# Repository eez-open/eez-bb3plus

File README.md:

### This is a WORK IN PROGRESS!

---

### Ownership and License
The contributors are listed in CONTRIB.TXT. 

Licenses | OSHWA UID
--|--
 | 

### Introduction

EEZ BB3+ was conceived as a successor to the BB3 project, which would bring a number of modifications and improvements. 
The following modifications are planned:

* [x] Combining 3 existing core modules ([power supply](https://github.com/eez-open/modular-psu/tree/master/aux-ps), [MCU](https://github.com/eez-open/modular-psu/tree/master/mcu) and [backplane](https://github.com/eez-open/modular-psu/tree/master/bp3c)) into a single mainboard
* [x] Enlarge TFT touchscreen from 4.3" (480x272) resistive to 5" (800x480) capacitive
* [x] Increase fan size from Ø80 to 92 mm
* [x] Single main power rail +12V (45/60 W)
* [x] Introducing half width modules and increasing the total number of modules from 3 full-width to 5 half-width (or two 1½-width)
* [x] TFT Display PCB with 4 user switch/hot keys

Planned new features of BB3+:

* [x] Max. 5 peripheral modules
* [x] Soft-power switch with standby indication
* [x] Isolated UART and RS485 port (with Modbus support) on the rear panel
* [x] Power/Sense terminals for the first two modules on the rear panel
* [x] MCU/CPU module slot [Raspberry Pi CM5](https://www.raspberrypi.com/products/compute-module-5/) compatible
* [x] M.2 slot, Key M (for NVMe SSD)
* [x] External display output (e.g. HDMI® or DisplayPort™ compatible): GUI and data could be displayed simultaneously on TFT and external display
* [x] 2.0/3.0 USB Hub with _FlexConnect_
* [x] 10/100/1000 Mbps Ethernet port
* [x] USB-C on the front panel, 2x USB 3 on the rear panel
* [x] Low-jitter 10 MHz reference clock
* [x] Trigger switch matrix (8 sources, 6 destinations)
* [x] New DIB specification for peripheral modules communication introducing USB HS/SS and PCIe
* **CE certified design**

### Modules

* [5" DVID TFT display](https://github.com/eez-open/eez-bb3plus/tree/main/KiCad/TFT%20module) module (HDMI® compatible input, optional EDID EEPROM, capacitive or optional resistive touchscreen)
* [BIO2210](https://github.com/eez-open/eez-bb3plus/tree/main/KiCad/BIO2210) Basic **non-isolated** I/O module: protected 8 analog inputs, 2 analog outputs, 8 multi-level (1.8 / 3.3 / 5 V) digital inputs, I2C/SMBus, 7 multi-level (1.8 / 3.3 V) digital outputs, 7 low-side switches, programmable clock, 3.3, 5 and 12V power outputs with reverse current blocking
* [DIB2 Adapter](https://github.com/eez-open/eez-bb3plus/tree/main/KiCad/DIB2%20adapter) module (USB3 Type A, DIB2 I/O, Reference clock)

### Experimental designs

During development, several prototypes will be used for features planned for BB3+. Information about them can be found in the [Experimental](https://github.com/eez-open/eez-bb3plus/tree/main/Experimental)  subfolder.

### Related topics and links

* [EEZ BB3+ MCU](https://github.com/eez-open/eez-bb3plus-cm5-mcu) module
* [DIB DCP405+](https://github.com/eez-open/dib-dcp405plus) power module
* [DIB MIO168+](https://github.com/eez-open/dib-mio168plus) mixed I/O module
* [EEZ BB3](https://github.com/eez-open/modular-psu)
* [EEZ Studio](https://www.envox.eu/studio/studio-introduction)
* [Discord](https://discord.com/invite/q5KAeeenNG) server
* [X](https://x.com/envox) (ex Twitter)
* [YouTube](https://www.youtube.com/c/eezopen) channel
* [EEVblog forum](https://www.eevblog.com/forum/projects/eez-h25005-a-possible-successor-of-eez-h24005-programmable-power-supply/) discussion

---

This work is financed by [NLnet](https://nlnet.nl/project/BB3-CM5/) foundation

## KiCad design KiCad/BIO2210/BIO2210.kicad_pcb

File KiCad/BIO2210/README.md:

Licenses | OSHWA UID
--|--
 | 

### BB3+ BIO2210 module

**Non-isolated**  Basic I/O module

* 32-bit MCU, 250 MHz
* 8-ch protected analog inputs (multiplexed): 2 x 0-100 V, 6 x 0-10 V
* 2-ch protected analog outputs near zero to 10 V
* 1.8 / 3.3 / 5 V logic level protected 8 digital input (alternative function: SPI and UART)
* 1.8 / 3.3 V logic level protected 7 digital outputs (alternative function: SPI, PWM, programmable clock output) + AC Freq output
* 7 low-side switches
* Protected 1.8 / 3.3 V I2C/SMBus interface
* 3.3V, 5V and 12V fused power outputs with reverse current blocking
* SPI and USB communication with BB3+ main processor
* Over-voltage fault indication for digital I/O

### Resources

* [Theory of operation](../../docs/BIO2210)
* [PDF Schematics](../../schematic-diagram/BIO2210.pdf)
* [Interactive BOM](../../fabrication/bom/BIO2210/ibom.html)

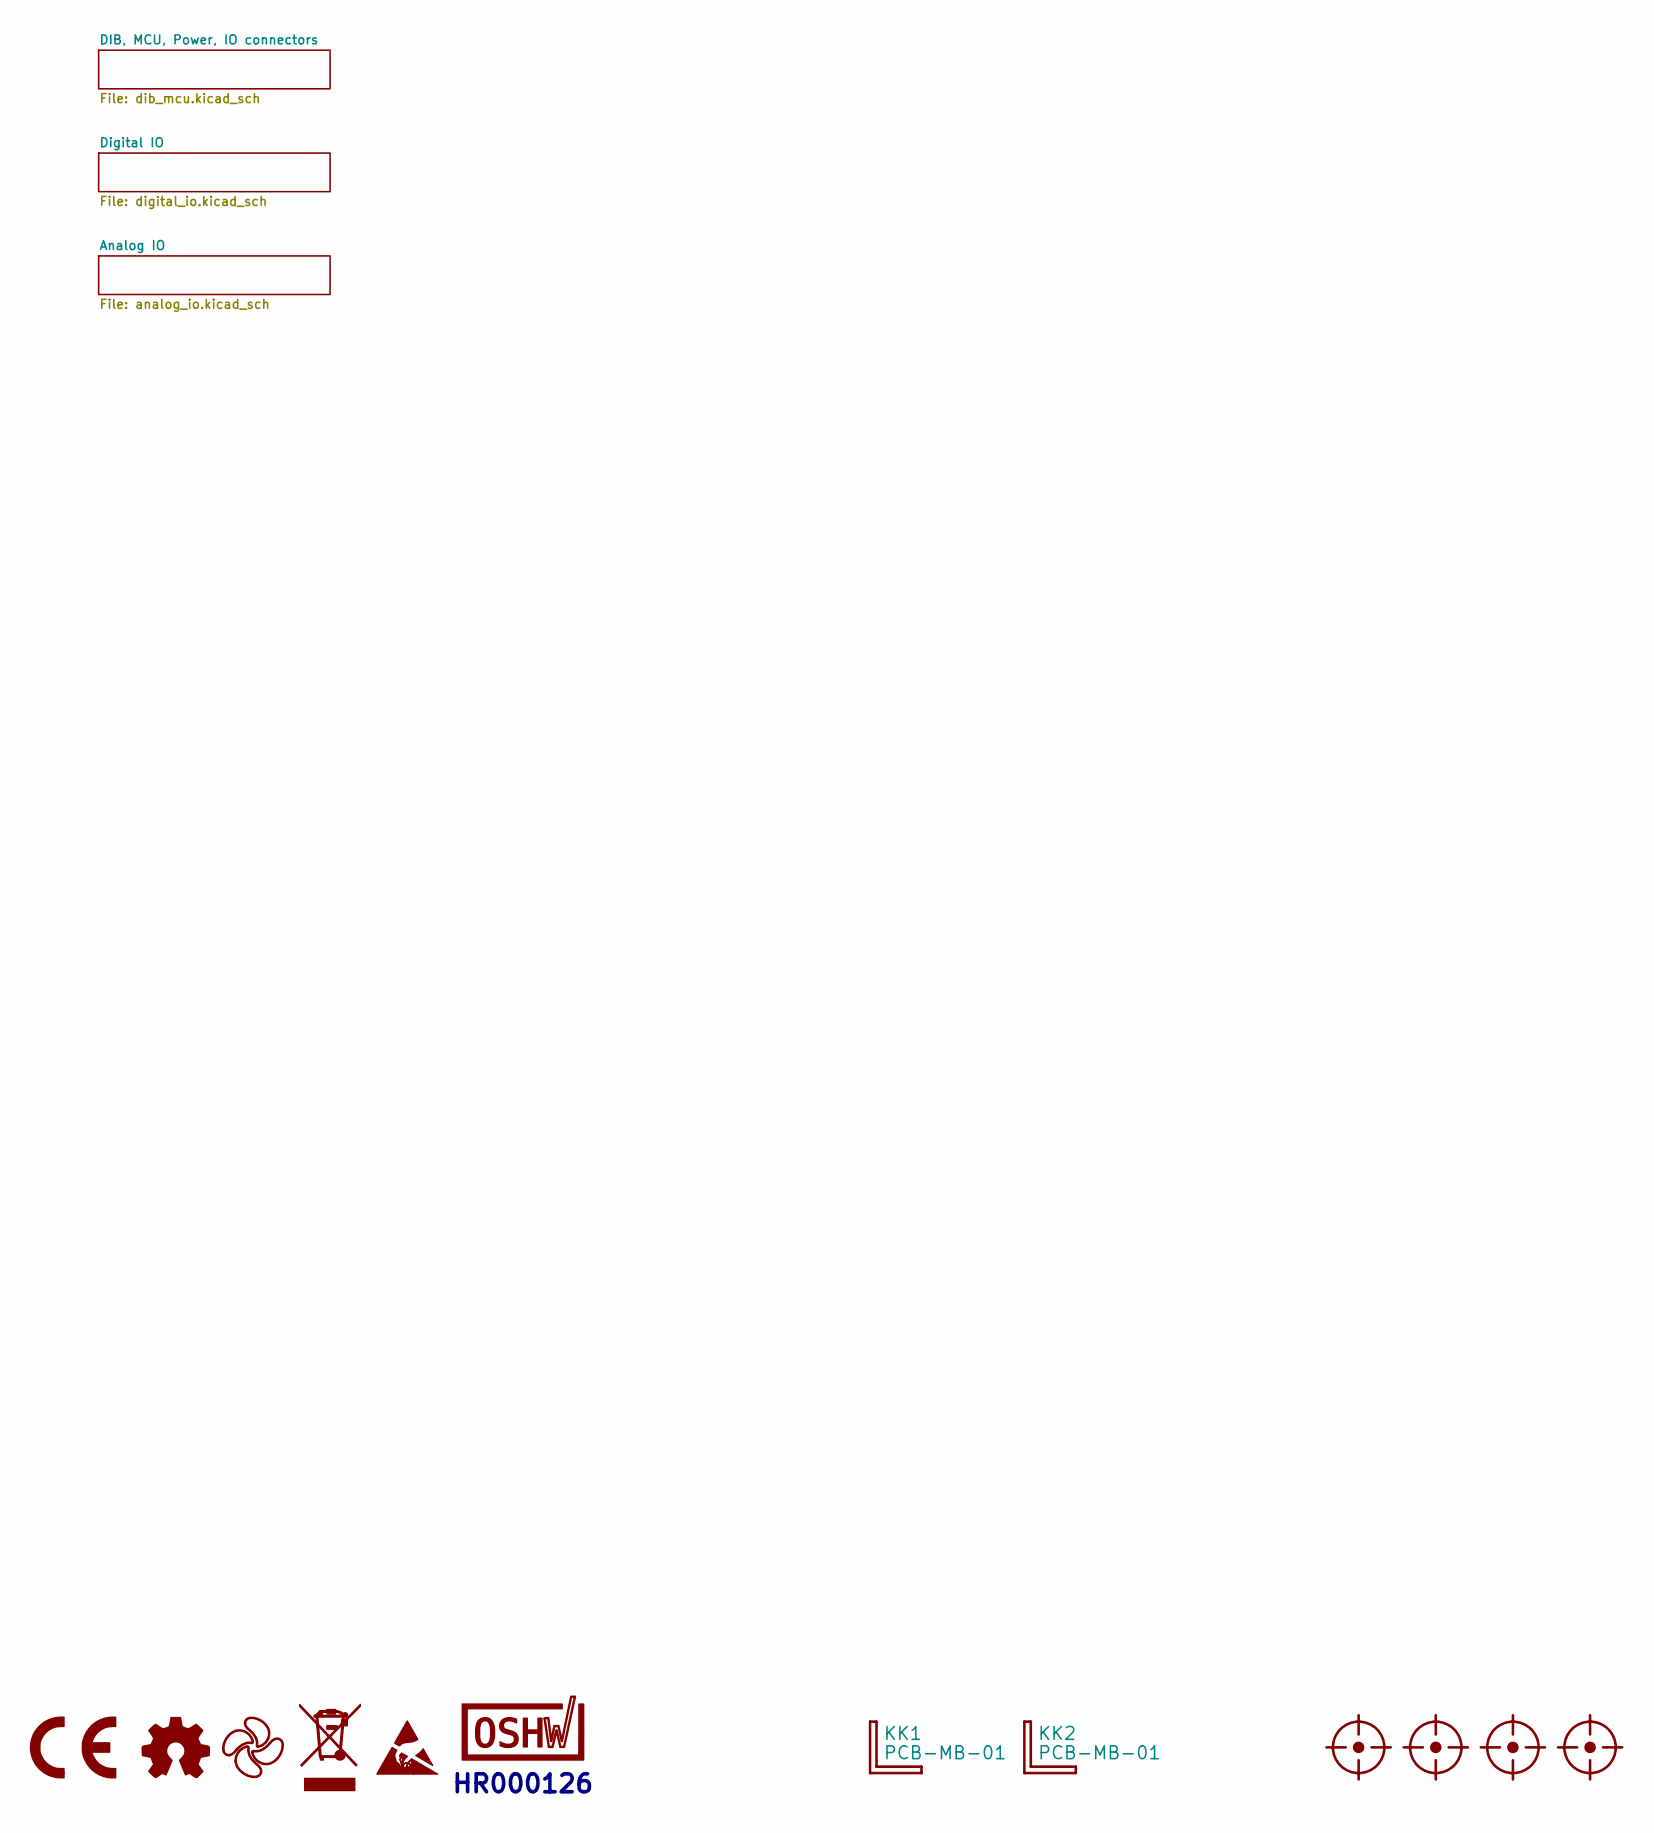
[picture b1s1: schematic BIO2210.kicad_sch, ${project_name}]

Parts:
FM1, FM2, FM3, FM4: FIDUCIAL; Fiducial_0.75mm_Mask1.5mm
KK1, KK2: PCB-MB-01; DigiKey RPC1760-ND
LOGO1: CR logo; CE logo
LOGO2: Open HW logo
LOGO3: EEZ logo; EEZ logo (outline 6mm)
LOGO4: WEEE logo
LOGO5: ESD logo
LOGO6: OSHWA logo; OSHWA logo 6.6mm

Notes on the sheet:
HR000126

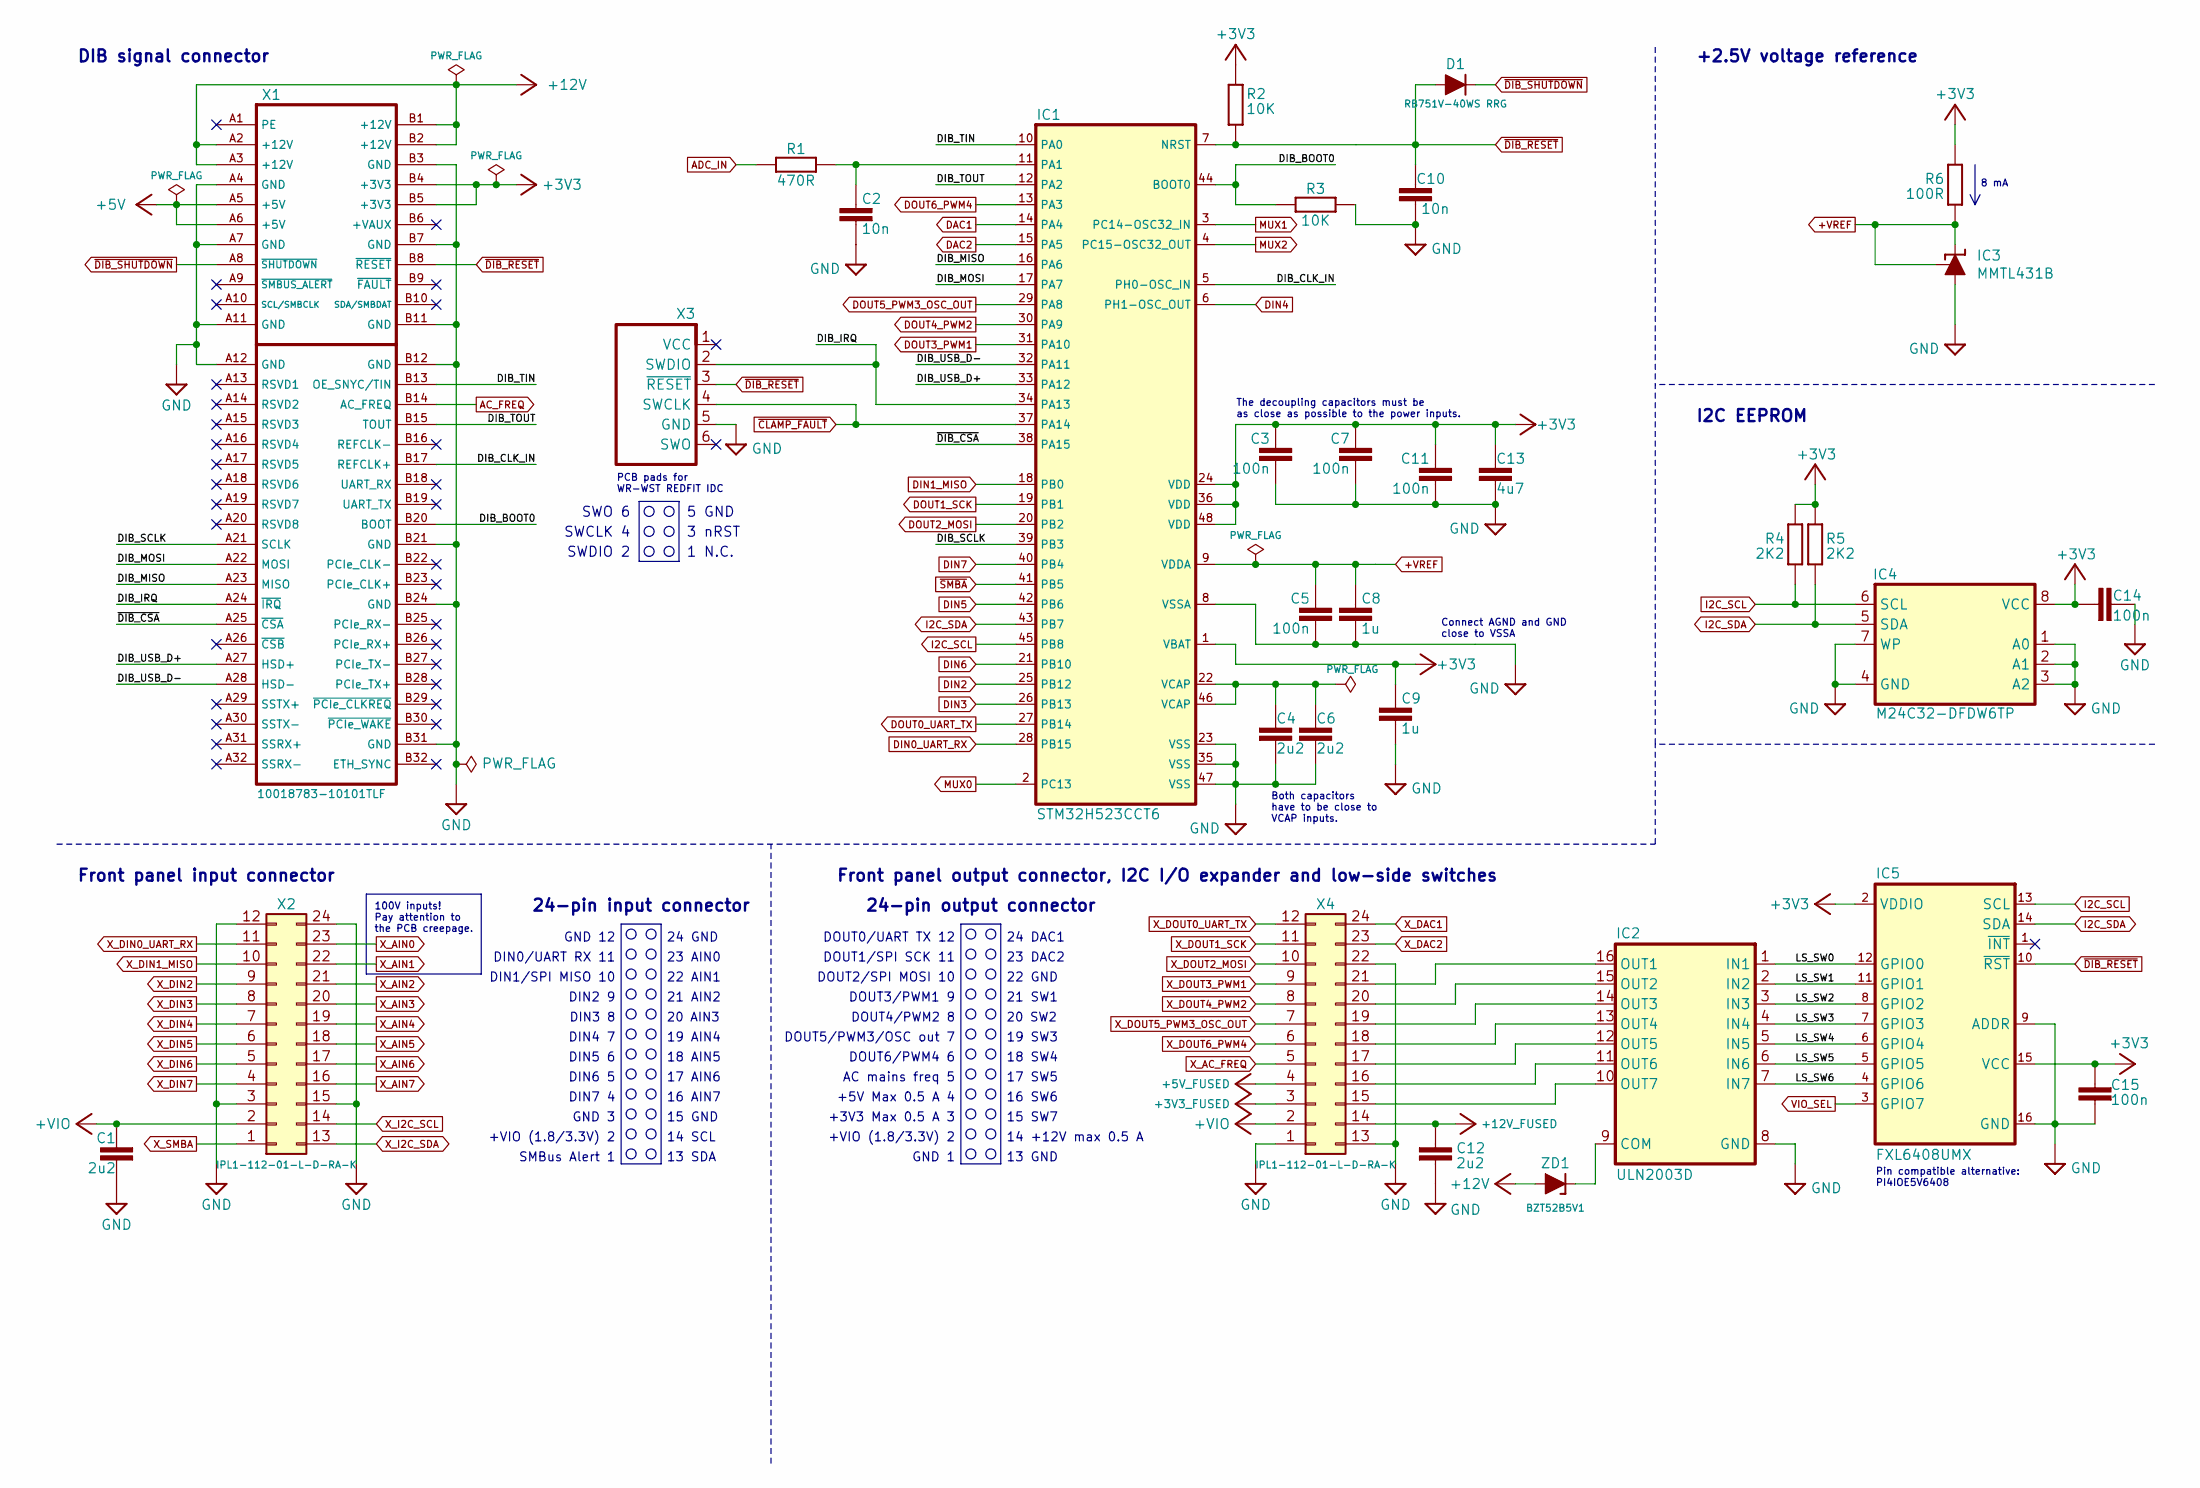
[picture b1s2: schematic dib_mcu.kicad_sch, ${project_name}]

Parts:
C1, C4, C6, C12: 2u2; C_0603_1608Metric; DigiKey 490-12332-1-ND
C2, C10: 10n; C_0603_1608Metric; DigiKey 1276-1009-1-ND
C3, C5, C7, C11, C14, C15: 100n; C_0603_1608Metric; DigiKey 1276-6717-1-ND
C8, C9: 1u; C_0603_1608Metric; DigiKey 1276-CL10A105KA8NFNCCT-ND
C13: 4u7; C_0805_2012Metric; DigiKey 1276-CL21A475KACLRNCCT-ND
D1: RB751V-40WS RRG; SOD-323_1P8X1P35_ONS-M; DigiKey RB751V-40WSRRGCT-ND
IC1: STM32H523CCT6; LQFP-48_7X7MM; DigiKey 497-STM32H523CCT6-ND
IC2: ULN2003D; SO16; DigiKey 497-2345-1-ND
IC3: MMTL431B; SOT103P240X110-3N; DigiKey 4878-MMTL431BCT-ND
IC4: M24C32-DFDW6TP; TSSOP-8; DigiKey 497-16067-1-ND
IC5: FXL6408UMX; UMLP16_1P8X2P6_ONS; DigiKey FXL6408UMXCT-ND
R1: 470R; R_1206_3216Metric; DigiKey RMCF1206FT470RCT-ND
R2, R3: 10K; R_0603_1608Metric; DigiKey 13-RC0603FR-1310KLCT-ND
R4, R5: 2K2; R_0603_1608Metric; DigiKey YAG1296CT-ND
R6: 100R; R_0603_1608Metric; DigiKey 13-RC0603FR-10100RLCT-ND
X1: 10018783-10101TLF; DIB 2.0 edge card connector
X2, X4: IPL1-112-01-L-D-RA-K; SAMTEC_IPL1-112-01-X-D-RA-K; DigiKey SAM9610-ND
X3: N.C.; WR-WST_490107670612_DEBUG
ZD1: BZT52B5V1; SOD123; DigiKey 5399-BZT52B5V1CT-ND

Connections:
+3V3: C3.1, C7.1, C9.2, C11.1, C13.1, C14.1, C15.2, IC1.1 (VBAT), IC1.24 (VDD), IC1.36 (VDD), IC1.48 (VDD), IC4.8 (VCC), IC5.2 (VDDIO), IC5.15 (VCC), R2.2, R4.1, R5.1, R6.2, X1.B4 (+3V3), X1.B5 (+3V3); also elsewhere on the board
+3V3_FUSED: X4.3; also elsewhere on the board
+5V: X1.A5 (+5V), X1.A6 (+5V); also elsewhere on the board
+5V_FUSED: X4.4; also elsewhere on the board
+12V: X1.A2 (+12V), X1.A3 (+12V), X1.B1 (+12V), X1.B2 (+12V), ZD1.A; also elsewhere on the board
+12V_FUSED: C12.2, X4.14; also elsewhere on the board
+VIO: C1.2, X2.2, X4.2; also elsewhere on the board
+VREF: C5.1, C8.2, IC1.9 (VDDA), IC3.1 (C), IC3.2 (R), R6.1; also elsewhere on the board
/DIB, MCU, Power, IO connectors/DIB_BOOT0: IC1.44 (BOOT0), R3.2, X1.B20 (BOOT)
/DIB, MCU, Power, IO connectors/DIB_CLK_IN: IC1.5 (PH0-OSC_IN), X1.B17 (REFCLK+)
/DIB, MCU, Power, IO connectors/DIB_IRQ: IC1.34 (PA13), X1.A24 (~IRQ), X3.2 (SWDIO)
/DIB, MCU, Power, IO connectors/DIB_MISO: IC1.16 (PA6), X1.A23 (MISO)
/DIB, MCU, Power, IO connectors/DIB_MOSI: IC1.17 (PA7), X1.A22 (MOSI)
/DIB, MCU, Power, IO connectors/DIB_SCLK: IC1.39 (PB3), X1.A21 (SCLK)
/DIB, MCU, Power, IO connectors/DIB_TIN: IC1.10 (PA0), X1.B13 (OE_SNYC/TIN)
/DIB, MCU, Power, IO connectors/DIB_TOUT: IC1.12 (PA2), X1.B15 (TOUT)
/DIB, MCU, Power, IO connectors/DIB_USB_D+: IC1.33 (PA12), X1.A27 (HSD+)
/DIB, MCU, Power, IO connectors/DIB_USB_D-: IC1.32 (PA11), X1.A28 (HSD-)
/DIB, MCU, Power, IO connectors/LS_SW0: IC2.1 (IN1), IC5.12 (GPIO0)
/DIB, MCU, Power, IO connectors/LS_SW1: IC2.2 (IN2), IC5.11 (GPIO1)
/DIB, MCU, Power, IO connectors/LS_SW2: IC2.3 (IN3), IC5.8 (GPIO2)
/DIB, MCU, Power, IO connectors/LS_SW3: IC2.4 (IN4), IC5.7 (GPIO3)
/DIB, MCU, Power, IO connectors/LS_SW4: IC2.5 (IN5), IC5.6 (GPIO4)
/DIB, MCU, Power, IO connectors/LS_SW5: IC2.6 (IN6), IC5.5 (GPIO5)
/DIB, MCU, Power, IO connectors/LS_SW6: IC2.7 (IN7), IC5.4 (GPIO6)
/DIB, MCU, Power, IO connectors/~DIB_CSA: IC1.38 (PA15), X1.A25 (~CSA)
AC_FREQ: X1.B14 (AC_FREQ); also elsewhere on the board
ADC_IN: R1.2; also elsewhere on the board
DAC1: IC1.14 (PA4); also elsewhere on the board
DAC2: IC1.15 (PA5); also elsewhere on the board
DIN0_UART_RX: IC1.28 (PB15); also elsewhere on the board
DIN1_MISO: IC1.18 (PB0); also elsewhere on the board
DIN2: IC1.25 (PB12); also elsewhere on the board
DIN3: IC1.26 (PB13); also elsewhere on the board
DIN4: IC1.6 (PH1-OSC_OUT); also elsewhere on the board
DIN5: IC1.42 (PB6); also elsewhere on the board
DIN6: IC1.21 (PB10); also elsewhere on the board
DIN7: IC1.40 (PB4); also elsewhere on the board
DOUT0_UART_TX: IC1.27 (PB14); also elsewhere on the board
DOUT1_SCK: IC1.19 (PB1); also elsewhere on the board
DOUT2_MOSI: IC1.20 (PB2); also elsewhere on the board
DOUT3_PWM1: IC1.31 (PA10); also elsewhere on the board
DOUT4_PWM2: IC1.30 (PA9); also elsewhere on the board
DOUT5_PWM3_OSC_OUT: IC1.29 (PA8); also elsewhere on the board
DOUT6_PWM4: IC1.13 (PA3); also elsewhere on the board
GND: C1.1, C2.2, C3.2, C4.1, C5.2, C6.1, C7.2, C8.1, C9.1, C10.1, C11.2, C12.1, C13.2, C14.2, C15.1, IC1.8 (VSSA), IC1.23 (VSS), IC1.35 (VSS), IC1.47 (VSS), IC2.8 (GND), IC3.3 (A), IC4.1 (A0), IC4.2 (A1), IC4.3 (A2), IC4.4 (GND), IC4.7 (WP), IC5.9 (ADDR), IC5.16 (GND), R3.1, X1.A4 (GND), X1.A7 (GND), X1.A11 (GND), X1.A12 (GND), X1.B3 (GND), X1.B7 (GND), X1.B11 (GND), X1.B12 (GND), X1.B21 (GND), X1.B24 (GND), X1.B31 (GND), X2.3, X2.12, X2.15, X2.24, X3.5 (GND), X4.1, X4.13, X4.22; also elsewhere on the board
I2C_SCL: IC1.45 (PB8), IC4.6 (SCL), IC5.13 (SCL), R4.2; also elsewhere on the board
I2C_SDA: IC1.43 (PB7), IC4.5 (SDA), IC5.14 (SDA), R5.2; also elsewhere on the board
MUX0: IC1.2 (PC13); also elsewhere on the board
MUX1: IC1.3 (PC14-OSC32_IN); also elsewhere on the board
MUX2: IC1.4 (PC15-OSC32_OUT); also elsewhere on the board
unnamed: C4.2, C6.2, IC1.22 (VCAP), IC1.46 (VCAP)
unnamed: C2.1, IC1.11 (PA1), R1.1
unnamed: IC2.9 (COM), ZD1.C
unnamed: IC2.16 (OUT1), X4.21
unnamed: IC2.15 (OUT2), X4.20
unnamed: IC2.14 (OUT3), X4.19
unnamed: IC2.13 (OUT4), X4.18
unnamed: IC2.12 (OUT5), X4.17
unnamed: IC2.11 (OUT6), X4.16
unnamed: IC2.10 (OUT7), X4.15
VIO_SEL: IC5.3 (GPIO7); also elsewhere on the board
X_AC_FREQ: X4.5; also elsewhere on the board
X_AIN0: X2.23; also elsewhere on the board
X_AIN1: X2.22; also elsewhere on the board
X_AIN2: X2.21; also elsewhere on the board
X_AIN3: X2.20; also elsewhere on the board
X_AIN4: X2.19; also elsewhere on the board
X_AIN5: X2.18; also elsewhere on the board
X_AIN6: X2.17; also elsewhere on the board
X_AIN7: X2.16; also elsewhere on the board
X_DAC1: X4.24; also elsewhere on the board
X_DAC2: X4.23; also elsewhere on the board
X_DIN0_UART_RX: X2.11; also elsewhere on the board
X_DIN1_MISO: X2.10; also elsewhere on the board
X_DIN2: X2.9; also elsewhere on the board
X_DIN3: X2.8; also elsewhere on the board
X_DIN4: X2.7; also elsewhere on the board
X_DIN5: X2.6; also elsewhere on the board
X_DIN6: X2.5; also elsewhere on the board
X_DIN7: X2.4; also elsewhere on the board
X_DOUT0_UART_TX: X4.12; also elsewhere on the board
X_DOUT1_SCK: X4.11; also elsewhere on the board
X_DOUT2_MOSI: X4.10; also elsewhere on the board
X_DOUT3_PWM1: X4.9; also elsewhere on the board
X_DOUT4_PWM2: X4.8; also elsewhere on the board
X_DOUT5_PWM3_OSC_OUT: X4.7; also elsewhere on the board
X_DOUT6_PWM4: X4.6; also elsewhere on the board
X_I2C_SCL: X2.14; also elsewhere on the board
X_I2C_SDA: X2.13; also elsewhere on the board
X_SMBA: X2.1; also elsewhere on the board
~CLAMP_FAULT: IC1.37 (PA14), X3.4 (SWCLK); also elsewhere on the board
~DIB_RESET: C10.2, D1.A, IC1.7 (NRST), IC5.10 (~RST), R2.1, X1.B8 (~RESET), X3.3 (~RESET)
~DIB_SHUTDOWN: D1.C, X1.A8 (~SHUTDOWN); also elsewhere on the board
~SMBA: IC1.41 (PB5); also elsewhere on the board

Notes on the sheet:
19 SW3
24 DAC1
SWCLK 4
GND 1
Both capacitors have to be close to VCAP inputs.
SWDIO 2
14 +12V max 0.5 A
DOUT3/PWM1 9
+2.5V voltage reference
14 SCL
Front panel input connector
8 mA
DIN1/SPI MISO 10
DIN3 8
16 SW6
I2C EEPROM
22 GND
DOUT1/SPI SCK 11
DOUT2/SPI MOSI 10
PCB pads for WR-WST REDFIT IDC
DIN7 4
SMBus Alert 1
3 nRST
SWO 6
Front panel output connector, I2C I/O expander and low-side switches
5 GND
23 DAC2
DIN2 9
19 AIN4
DIN6 5
18 SW4
17 SW5
20 SW2
17 AIN6
+VIO (1.8/3.3V) 2
24-pin output connector
DOUT4/PWM2 8
DIN0/UART RX 11
DOUT0/UART TX 12
24-pin input connector

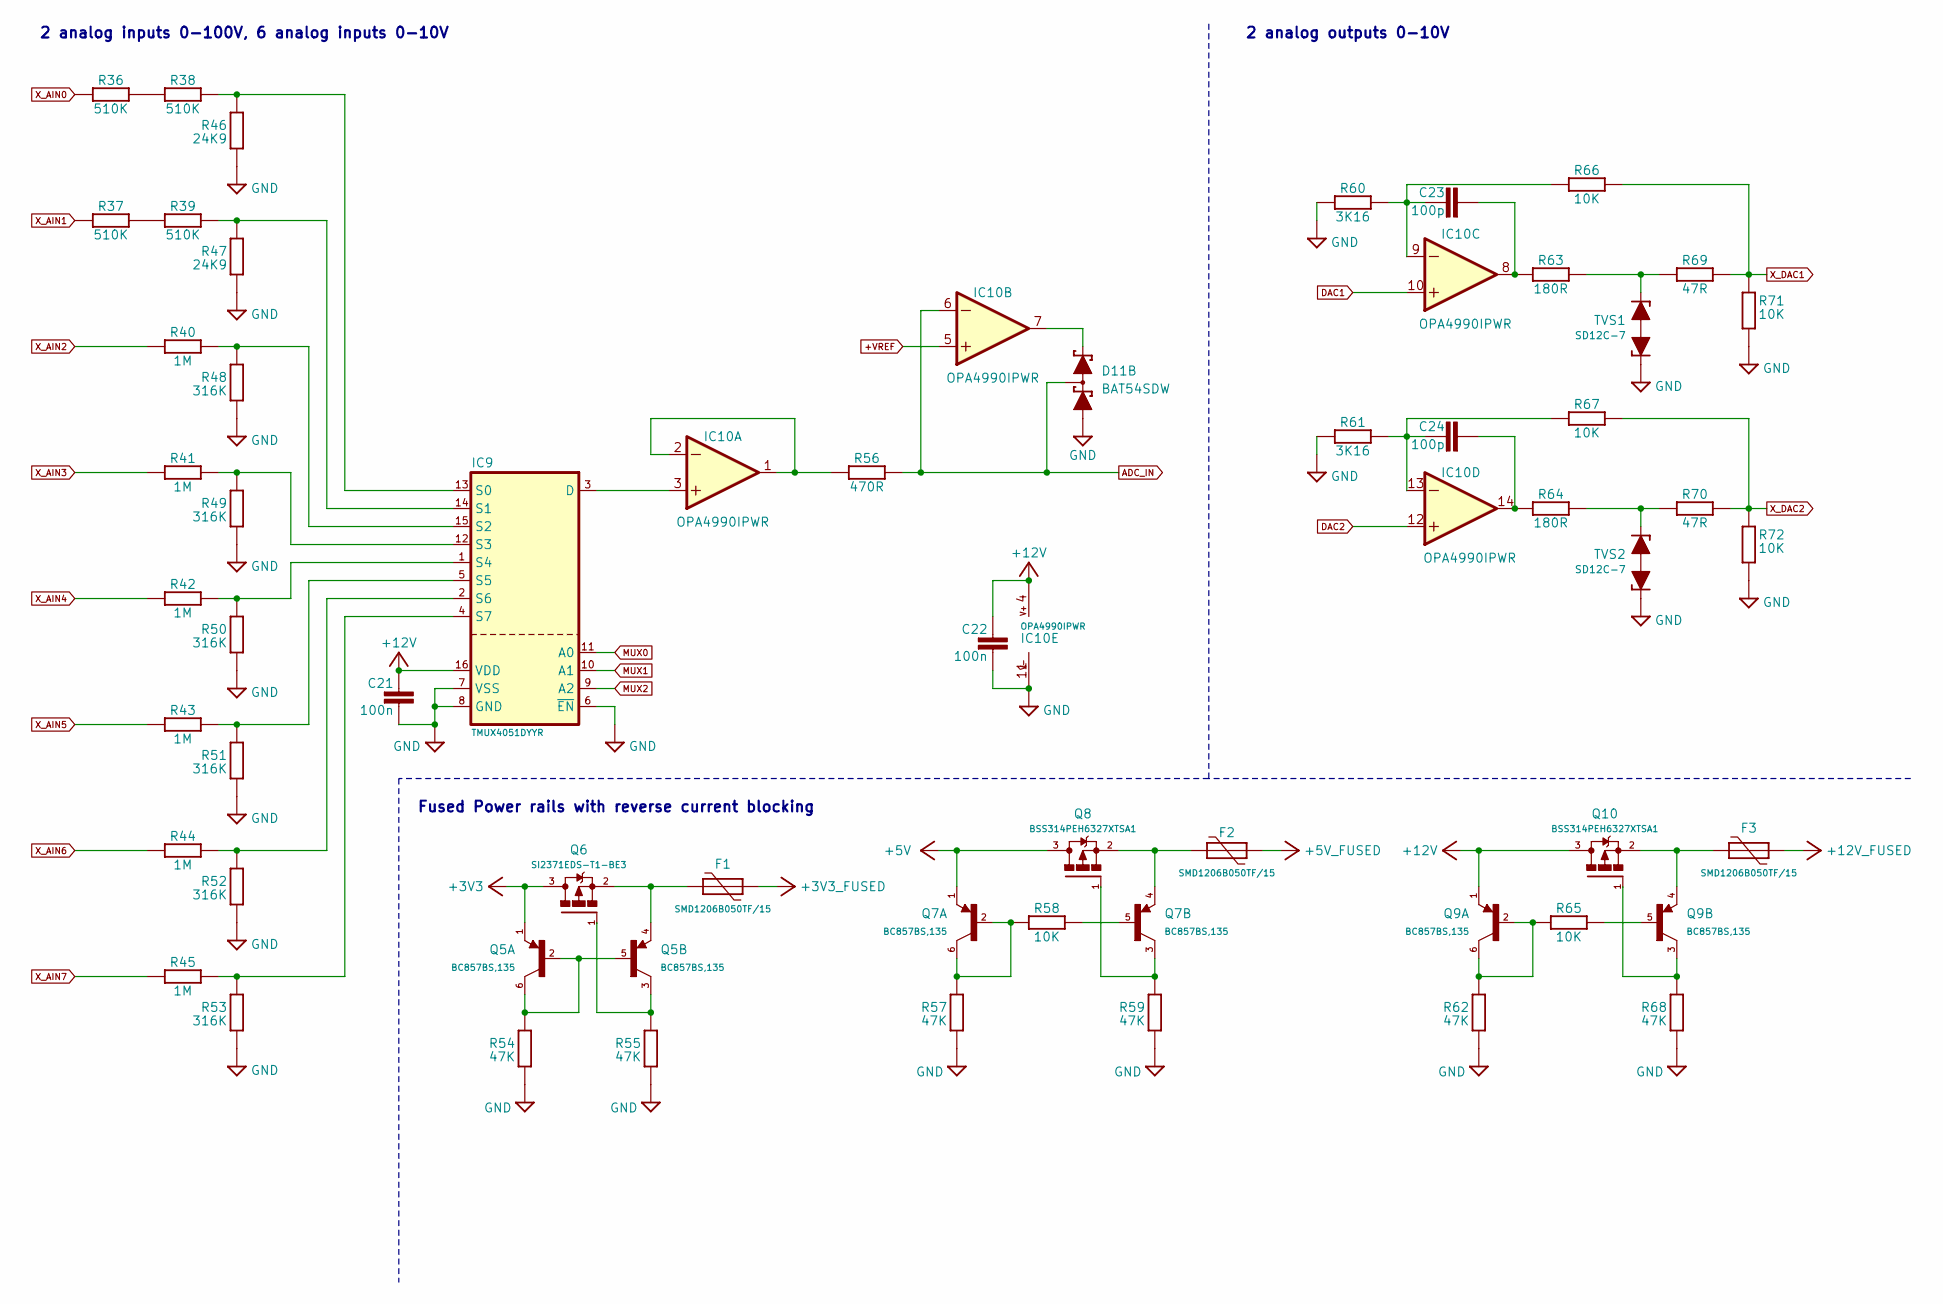
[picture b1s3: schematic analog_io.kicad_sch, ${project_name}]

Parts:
C21, C22: 100n; C_0603_1608Metric; DigiKey 1276-6717-1-ND
C23, C24: 100p; C_0603_1608Metric; DigiKey 1276-1295-1-ND
D11: BAT54SDW; SOP65P210X110-6N; DigiKey 3757-BAT54SDW_R1_00001CT-ND
F1, F2, F3: SMD1206B050TF/15; Fuse_1206; DigiKey 13-SMD1206B050TF/15CT-ND
IC9: TMUX4051DYYR; SOT-23-THIN16_DYY_TEX; DigiKey 296-TMUX4051DYYRCT-ND
IC10: OPA4990IPWR; PW14; DigiKey 296-OPA4990IPWRCT-ND
Q5, Q7, Q9: BC857BS,135; SOT65P210X110-6N; DigiKey 1727-1881-1-ND
Q6: SI2371EDS-T1-BE3; SOT23-3; DigiKey 742-SI2371EDS-T1-BE3CT-ND
Q8, Q10: BSS314PEH6327XTSA1; SOT23-3; DigiKey BSS314PEH6327XTSA1CT-ND
R36, R37, R38, R39: 510K; R_1206_3216Metric; DigiKey RMCF1206FT510KCT-ND
R40, R41, R42, R43, R44, R45: 1M; R_1206_3216Metric; DigiKey RMCF1206FT1M00CT-ND
R46, R47: 24K9; R_1206_3216Metric; DigiKey RMCF1206FT24K9CT-ND
R48, R49, R50, R51, R52, R53: 316K; R_1206_3216Metric; DigiKey 738-RMCF1206FT316KCT-ND
R54, R55, R57, R59, R62, R68: 47K; R_0603_1608Metric; DigiKey 13-RC0603FR-1347KLCT-ND
R56: 470R; R_1206_3216Metric; DigiKey RMCF1206FT470RCT-ND
R58, R65, R66, R67, R71, R72: 10K; R_0603_1608Metric; DigiKey 13-RC0603FR-1310KLCT-ND
R60, R61: 3K16; R_0603_1608Metric; DigiKey 311-3.16KHRCT-ND
R63, R64: 180R; R_1206_3216Metric; DigiKey 13-RC1206FR-13180RLCT-ND
R69, R70: 47R; R_0805_2012Metric; DigiKey 311-47.0CRCT-ND
TVS1, TVS2: SD12C-7; SOD-323_PESD; DigiKey 31-SD12C-7CT-ND

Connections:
+3V3: Q5.1 (E1), Q6.3 (D); also elsewhere on the board
+3V3_FUSED: F1.1; also elsewhere on the board
+5V: Q7.1 (E1), Q8.3 (D); also elsewhere on the board
+5V_FUSED: F2.1; also elsewhere on the board
+12V: C21.1, C22.1, IC9.16 (VDD), IC10.4 (V+), Q9.1 (E1), Q10.3 (D); also elsewhere on the board
+12V_FUSED: F3.1; also elsewhere on the board
+VREF: IC10.5 (+IN); also elsewhere on the board
ADC_IN: D11.3 (A3K4), IC10.6 (-IN), R56.1; also elsewhere on the board
DAC1: IC10.10 (+IN); also elsewhere on the board
DAC2: IC10.12 (+IN); also elsewhere on the board
GND: C21.2, C22.2, D11.4 (A4), IC9.6 (~EN), IC9.7 (VSS), IC9.8 (GND), IC10.11 (V-), R46.1, R47.1, R48.1, R49.1, R50.1, R51.1, R52.1, R53.1, R54.2, R55.2, R57.2, R59.2, R60.2, R61.2, R62.2, R68.2, R71.1, R72.1, TVS1.C1 (1), TVS2.C1 (1); also elsewhere on the board
MUX0: IC9.11 (A0); also elsewhere on the board
MUX1: IC9.10 (A1); also elsewhere on the board
MUX2: IC9.9 (A2); also elsewhere on the board
unnamed: D11.5 (K3), IC10.7 (OUT)
unnamed: IC9.13 (S0), R38.1, R46.2
unnamed: IC9.14 (S1), R39.1, R47.2
unnamed: IC9.15 (S2), R40.1, R48.2
unnamed: IC9.12 (S3), R41.1, R49.2
unnamed: IC9.1 (S4), R42.1, R50.2
unnamed: IC9.5 (S5), R43.1, R51.2
unnamed: IC9.2 (S6), R44.1, R52.2
unnamed: IC9.4 (S7), R45.1, R53.2
unnamed: IC9.3 (D), IC10.3 (+IN)
unnamed: IC10.1 (OUT), IC10.2 (-IN), R56.2
unnamed: C23.2, IC10.9 (-IN), R60.1, R66.2
unnamed: C23.1, IC10.8 (OUT), R63.2
unnamed: C24.2, IC10.13 (-IN), R61.1, R67.2
unnamed: C24.1, IC10.14 (OUT), R64.2
unnamed: Q5.2 (B1), Q5.5 (B2), Q5.6 (C1), R54.1
unnamed: Q5.3 (C2), Q6.1 (G), R55.1
unnamed: F1.2, Q5.4 (E2), Q6.2 (S)
unnamed: Q7.2 (B1), Q7.6 (C1), R57.1, R58.2
unnamed: Q7.5 (B2), R58.1
unnamed: Q7.3 (C2), Q8.1 (G), R59.1
unnamed: F2.2, Q7.4 (E2), Q8.2 (S)
unnamed: Q9.2 (B1), Q9.6 (C1), R62.1, R65.2
unnamed: Q9.5 (B2), R65.1
unnamed: Q9.3 (C2), Q10.1 (G), R68.1
unnamed: F3.2, Q9.4 (E2), Q10.2 (S)
unnamed: R36.1, R38.2
unnamed: R37.1, R39.2
unnamed: R63.1, R69.2, TVS1.C2 (2)
unnamed: R64.1, R70.2, TVS2.C2 (2)
X_AIN0: R36.2; also elsewhere on the board
X_AIN1: R37.2; also elsewhere on the board
X_AIN2: R40.2; also elsewhere on the board
X_AIN3: R41.2; also elsewhere on the board
X_AIN4: R42.2; also elsewhere on the board
X_AIN5: R43.2; also elsewhere on the board
X_AIN6: R44.2; also elsewhere on the board
X_AIN7: R45.2; also elsewhere on the board
X_DAC1: R66.1, R69.1, R71.2; also elsewhere on the board
X_DAC2: R67.1, R70.1, R72.2; also elsewhere on the board

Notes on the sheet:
2 analog inputs 0-100V, 6 analog inputs 0-10V
2 analog outputs 0-10V
Fused Power rails with reverse current blocking

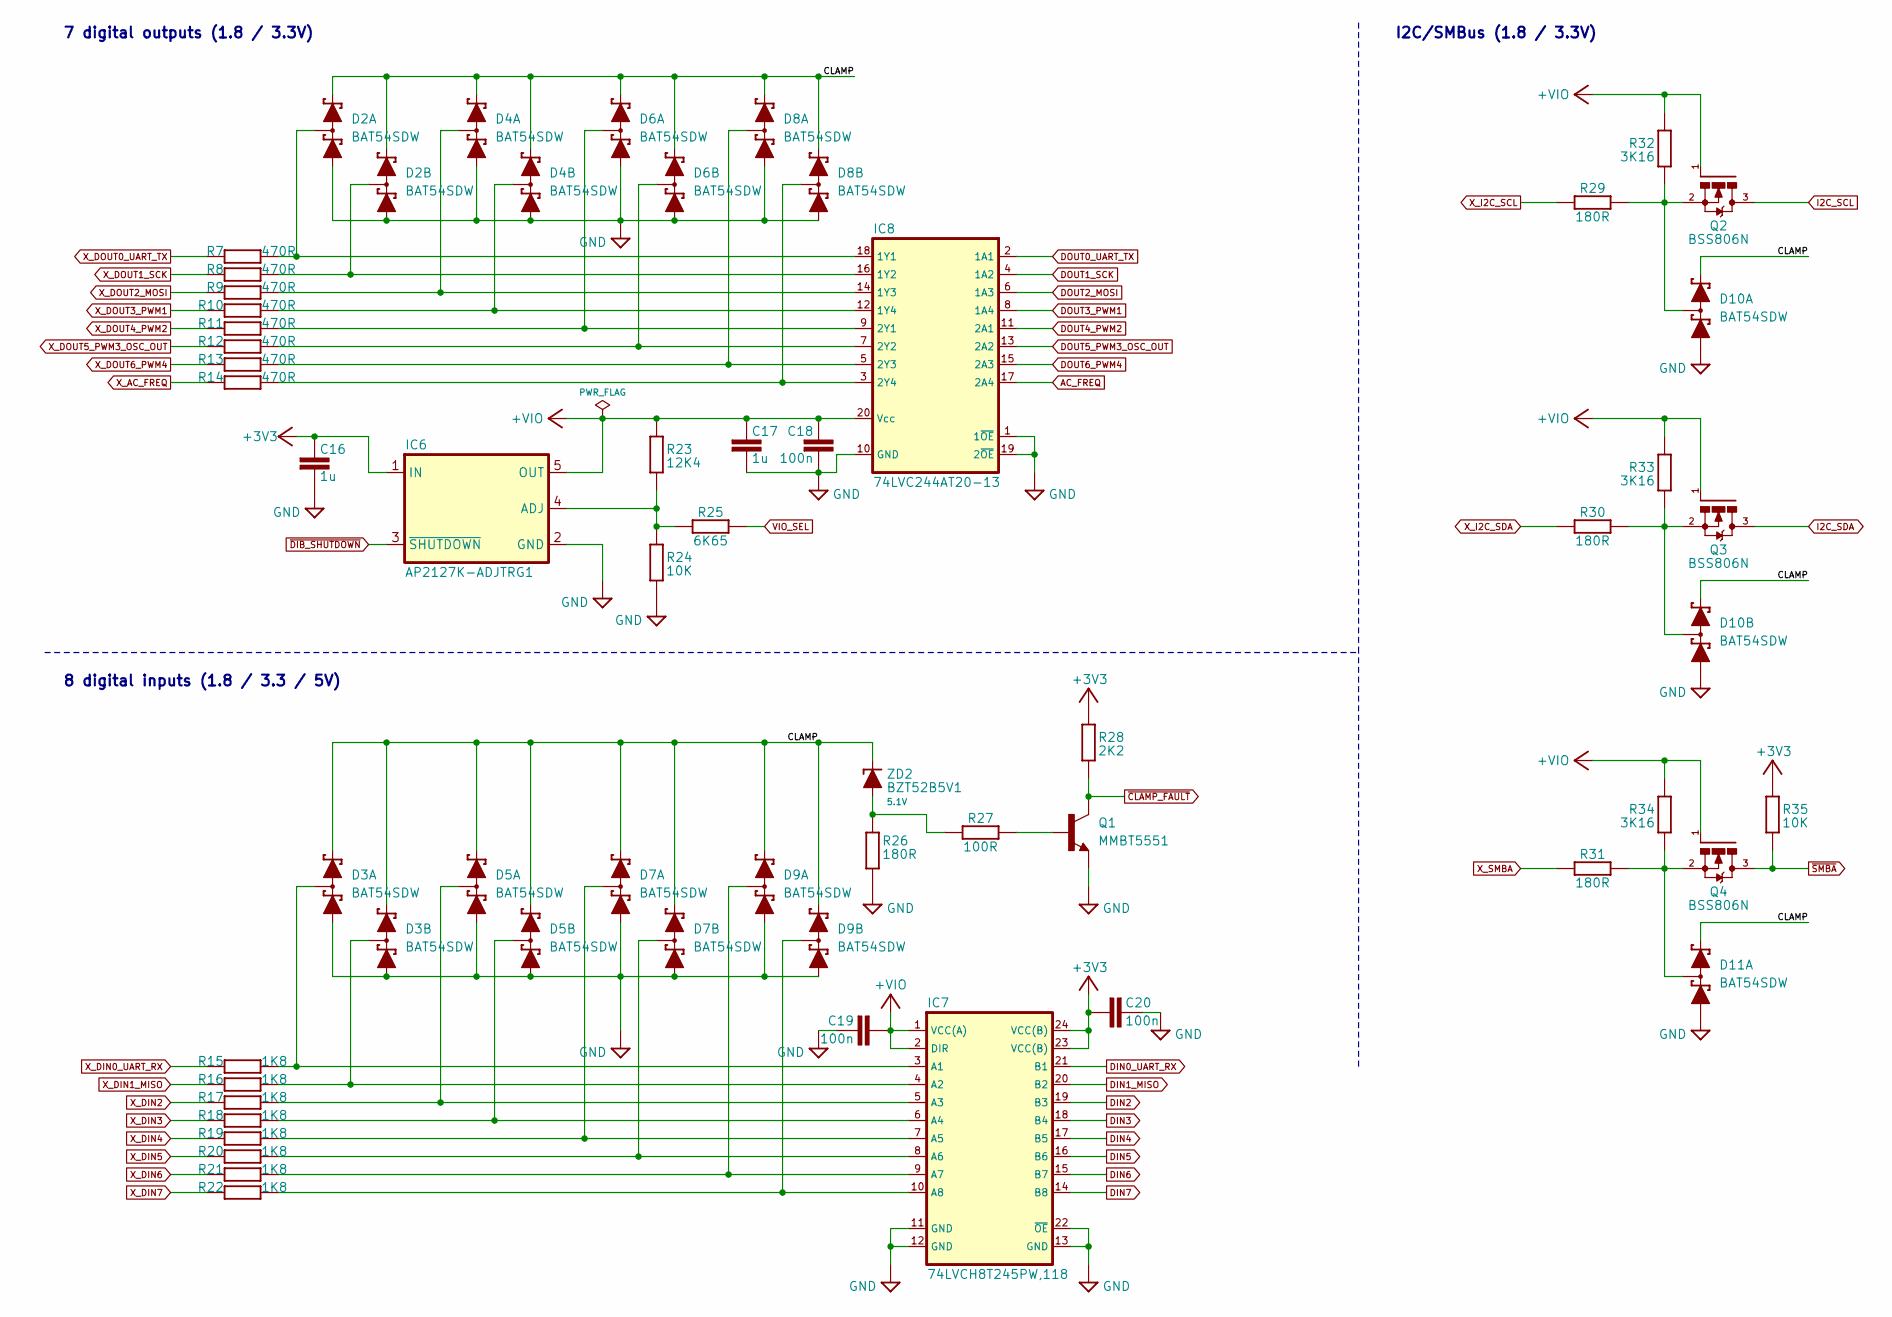
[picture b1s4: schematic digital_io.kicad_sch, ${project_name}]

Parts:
C16, C17: 1u; C_0603_1608Metric; DigiKey 1276-CL10A105KA8NFNCCT-ND
C18, C19, C20: 100n; C_0603_1608Metric; DigiKey 1276-6717-1-ND
D2, D3, D4, D5, D6, D7, D8, D9, D10, D11: BAT54SDW; SOP65P210X110-6N; DigiKey 3757-BAT54SDW_R1_00001CT-ND
IC6: AP2127K-ADJTRG1; DBV5; DigiKey AP2127K-ADJTRG1DICT-ND
IC7: 74LVCH8T245PW,118; TSSOP-24; DigiKey 1727-4419-1-ND
IC8: 74LVC244AT20-13; TSSOP-20; DigiKey 31-74LVC244AT20-13CT-ND
Q1: MMBT5551; SOT23-BEC; DigiKey MMBT5551LT1GOSCT-ND
Q2, Q3, Q4: BSS806N; SOT103P240X110-3N; DigiKey BSS806NEH6327XTSA1CT-ND
R7, R8, R9, R10, R11, R12, R13, R14: 470R; R_1206_3216Metric; DigiKey RMCF1206FT470RCT-ND
R15, R16, R17, R18, R19, R20, R21, R22: 1K8; R_1206_3216Metric; DigiKey RMCF1206FT1K80CT-ND
R23: 12K4; R_0603_1608Metric; DigiKey 311-12.4KMCT-ND
R24, R35: 10K; R_0603_1608Metric; DigiKey 13-RC0603FR-1310KLCT-ND
R25: 6K65; R_0603_1608Metric; DigiKey 311-6.65KHRCT-ND
R26, R29, R30, R31: 180R; R_1206_3216Metric; DigiKey 13-RC1206FR-13180RLCT-ND
R27: 100R; R_0603_1608Metric; DigiKey 13-RC0603FR-10100RLCT-ND
R28: 2K2; R_0603_1608Metric; DigiKey YAG1296CT-ND
R32, R33, R34: 3K16; R_0603_1608Metric; DigiKey 311-3.16KHRCT-ND
ZD2: BZT52B5V1; SOD123; DigiKey 5399-BZT52B5V1CT-ND

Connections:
+3V3: C16.2, C20.1, IC6.1 (IN), IC7.23 (VCC(B)), IC7.24 (VCC(B)), R28.2, R35.2; also elsewhere on the board
+VIO: C17.2, C18.1, C19.1, IC6.5 (OUT), IC7.1 (VCC(A)), IC7.2 (DIR), IC8.20 (Vcc), Q2.1 (G), Q3.1 (G), Q4.1 (G), R23.2, R32.1, R33.1, R34.1; also elsewhere on the board
/Digital IO/CLAMP: D2.2 (K2), D2.5 (K3), D3.2 (K2), D3.5 (K3), D4.2 (K2), D4.5 (K3), D5.2 (K2), D5.5 (K3), D6.2 (K2), D6.5 (K3), D7.2 (K2), D7.5 (K3), D8.2 (K2), D8.5 (K3), D9.2 (K2), D9.5 (K3), D10.2 (K2), D10.5 (K3), D11.2 (K2), ZD2.C
AC_FREQ: IC8.17 (2A4); also elsewhere on the board
DIN0_UART_RX: IC7.21 (B1); also elsewhere on the board
DIN1_MISO: IC7.20 (B2); also elsewhere on the board
DIN2: IC7.19 (B3); also elsewhere on the board
DIN3: IC7.18 (B4); also elsewhere on the board
DIN4: IC7.17 (B5); also elsewhere on the board
DIN5: IC7.16 (B6); also elsewhere on the board
DIN6: IC7.15 (B7); also elsewhere on the board
DIN7: IC7.14 (B8); also elsewhere on the board
DOUT0_UART_TX: IC8.2 (1A1); also elsewhere on the board
DOUT1_SCK: IC8.4 (1A2); also elsewhere on the board
DOUT2_MOSI: IC8.6 (1A3); also elsewhere on the board
DOUT3_PWM1: IC8.8 (1A4); also elsewhere on the board
DOUT4_PWM2: IC8.11 (2A1); also elsewhere on the board
DOUT5_PWM3_OSC_OUT: IC8.13 (2A2); also elsewhere on the board
DOUT6_PWM4: IC8.15 (2A3); also elsewhere on the board
GND: C16.1, C17.1, C18.2, C19.2, C20.2, D2.1 (A1), D2.4 (A4), D3.1 (A1), D3.4 (A4), D4.1 (A1), D4.4 (A4), D5.1 (A1), D5.4 (A4), D6.1 (A1), D6.4 (A4), D7.1 (A1), D7.4 (A4), D8.1 (A1), D8.4 (A4), D9.1 (A1), D9.4 (A4), D10.1 (A1), D10.4 (A4), D11.1 (A1), IC6.2 (GND), IC7.11 (GND), IC7.12 (GND), IC7.13 (GND), IC7.22 (~OE), IC8.1 (1~OE), IC8.10 (GND), IC8.19 (2~OE), Q1.E, R24.1, R26.1; also elsewhere on the board
I2C_SCL: Q2.3 (D); also elsewhere on the board
I2C_SDA: Q3.3 (D); also elsewhere on the board
unnamed: D2.6 (K1A2), IC8.18 (1Y1), R7.2
unnamed: D2.3 (A3K4), IC8.16 (1Y2), R8.2
unnamed: D3.6 (K1A2), IC7.3 (A1), R15.2
unnamed: D3.3 (A3K4), IC7.4 (A2), R16.2
unnamed: D4.6 (K1A2), IC8.14 (1Y3), R9.2
unnamed: D4.3 (A3K4), IC8.12 (1Y4), R10.2
unnamed: D5.6 (K1A2), IC7.5 (A3), R17.2
unnamed: D5.3 (A3K4), IC7.6 (A4), R18.2
unnamed: D6.6 (K1A2), IC8.9 (2Y1), R11.2
unnamed: D6.3 (A3K4), IC8.7 (2Y2), R12.2
unnamed: D7.6 (K1A2), IC7.7 (A5), R19.2
unnamed: D7.3 (A3K4), IC7.8 (A6), R20.2
unnamed: D8.6 (K1A2), IC8.5 (2Y3), R13.2
unnamed: D8.3 (A3K4), IC8.3 (2Y4), R14.2
unnamed: D9.6 (K1A2), IC7.9 (A7), R21.2
unnamed: D9.3 (A3K4), IC7.10 (A8), R22.2
unnamed: D10.6 (K1A2), Q2.2 (S), R29.2, R32.2
unnamed: D10.3 (A3K4), Q3.2 (S), R30.2, R33.2
unnamed: D11.6 (K1A2), Q4.2 (S), R31.2, R34.2
unnamed: IC6.4 (ADJ), R23.1, R24.2, R25.1
unnamed: Q1.B, R27.2
unnamed: R26.2, R27.1, ZD2.A
VIO_SEL: R25.2; also elsewhere on the board
X_AC_FREQ: R14.1; also elsewhere on the board
X_DIN0_UART_RX: R15.1; also elsewhere on the board
X_DIN1_MISO: R16.1; also elsewhere on the board
X_DIN2: R17.1; also elsewhere on the board
X_DIN3: R18.1; also elsewhere on the board
X_DIN4: R19.1; also elsewhere on the board
X_DIN5: R20.1; also elsewhere on the board
X_DIN6: R21.1; also elsewhere on the board
X_DIN7: R22.1; also elsewhere on the board
X_DOUT0_UART_TX: R7.1; also elsewhere on the board
X_DOUT1_SCK: R8.1; also elsewhere on the board
X_DOUT2_MOSI: R9.1; also elsewhere on the board
X_DOUT3_PWM1: R10.1; also elsewhere on the board
X_DOUT4_PWM2: R11.1; also elsewhere on the board
X_DOUT5_PWM3_OSC_OUT: R12.1; also elsewhere on the board
X_DOUT6_PWM4: R13.1; also elsewhere on the board
X_I2C_SCL: R29.1; also elsewhere on the board
X_I2C_SDA: R30.1; also elsewhere on the board
X_SMBA: R31.1; also elsewhere on the board
~CLAMP_FAULT: Q1.C, R28.1; also elsewhere on the board
~DIB_SHUTDOWN: IC6.3 (~SHUTDOWN); also elsewhere on the board
~SMBA: Q4.3 (D), R35.1; also elsewhere on the board

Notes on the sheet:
I2C/SMBus (1.8 / 3.3V)
8 digital inputs (1.8 / 3.3 / 5V)
7 digital outputs (1.8 / 3.3V)

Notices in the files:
parts and their libraries:
project_license: Licensed under the TAPR Open Hardware License (www.tapr.org/OHL)
